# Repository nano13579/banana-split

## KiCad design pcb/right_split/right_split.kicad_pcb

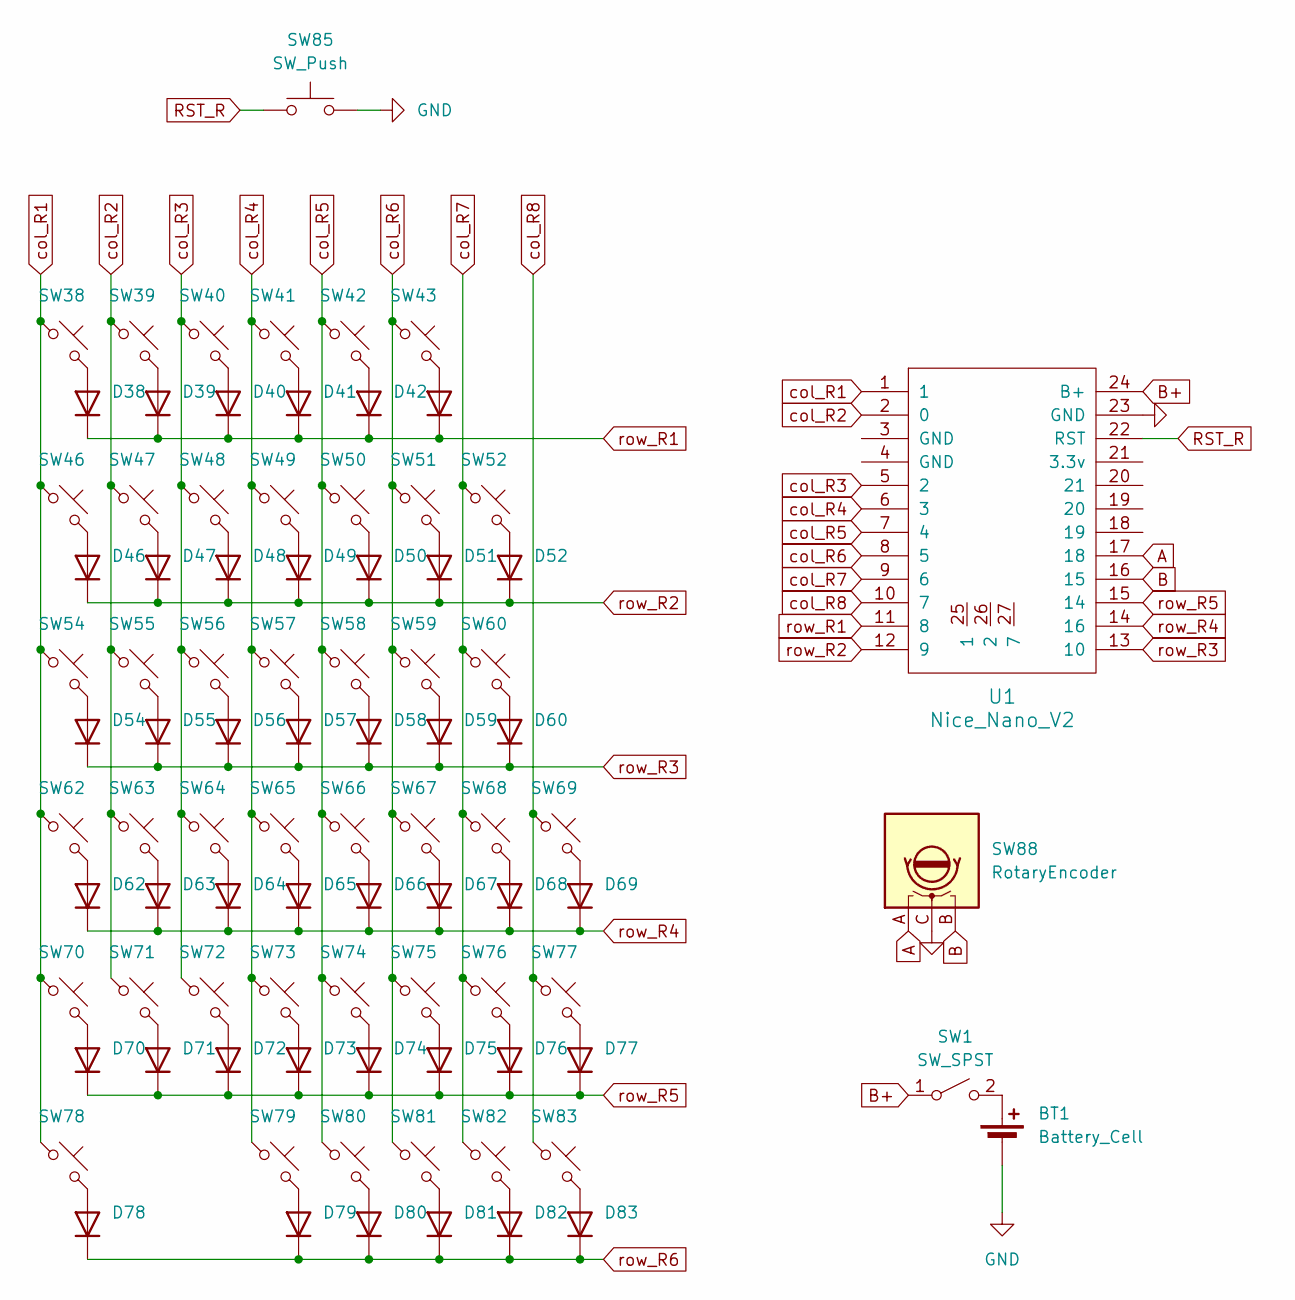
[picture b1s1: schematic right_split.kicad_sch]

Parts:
BT1: Battery_Cell; JST_PH_S2B-PH-K_1x02_P2.00mm_Horizontal
D38, D39, D40, D41, D42, D43, D46, D47, D48, D49, D50, D51, D52, D54, D55, D56, D57, D58, D59, D60, D62, D63, D64, D65, D66, D67, D68, D69, D70, D71, D72, D73, D74, D75, D76, D77, D78, D79, D80, D81, D82, D83: 1N4148; D_DO-35_SOD27_P7.62mm_Horizontal
SW1: SW_SPST; SW_SPST_Omron_B3F-40xx
SW38, SW39, SW40, SW41, SW42, SW43, SW46, SW47, SW48, SW49, SW50, SW51, SW54, SW55, SW56, SW57, SW58, SW59, SW62, SW63, SW64, SW65, SW66, SW67, SW69, SW70, SW71, SW72, SW73, SW74, SW76, SW77, SW83: SW_Push_45deg; MX-Hotswap-1U
SW52: SW_Push_45deg; MX-Hotswap-2U
SW60, SW82: SW_Push_45deg; MX-Hotswap-1.5U
SW68: SW_Push_45deg; MX-Hotswap-2.25U
SW75: SW_Push_45deg; MX-Hotswap-1.75U
SW78: SW_Push_45deg; MX-Hotswap-3U
SW79, SW80, SW81: SW_Push_45deg; MX-Hotswap-1.25U
SW85: SW_Push; SW_PUSH_6mm
SW88: RotaryEncoder; RotaryEncoder_Alps_EC11E-Switch_Vertical_H20mm
U1: Nice_Nano_V2

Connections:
A: SW88.A, U1.17 (18)
B: SW88.B, U1.16 (15)
B+: SW1.1 (A), U1.24 (B+)
GND: BT1.2 (-), SW85.2
GND_MCU2: SW88.C, U1.23 (GND)
unnamed: BT1.1 (+), SW1.2 (B)
unnamed: D38.2 (A), SW38.2
unnamed: D39.2 (A), SW39.2
unnamed: D40.2 (A), SW40.2
unnamed: D41.2 (A), SW41.2
unnamed: D42.2 (A), SW42.2
unnamed: D43.2 (A), SW43.2
unnamed: D46.2 (A), SW46.2
unnamed: D47.2 (A), SW47.2
unnamed: D48.2 (A), SW48.2
unnamed: D49.2 (A), SW49.2
unnamed: D50.2 (A), SW50.2
unnamed: D51.2 (A), SW51.2
unnamed: D52.2 (A), SW52.2
unnamed: D54.2 (A), SW54.2
unnamed: D55.2 (A), SW55.2
unnamed: D56.2 (A), SW56.2
unnamed: D57.2 (A), SW57.2
unnamed: D58.2 (A), SW58.2
unnamed: D59.2 (A), SW59.2
unnamed: D60.2 (A), SW60.2
unnamed: D62.2 (A), SW62.2
unnamed: D63.2 (A), SW63.2
unnamed: D64.2 (A), SW64.2
unnamed: D65.2 (A), SW65.2
unnamed: D66.2 (A), SW66.2
unnamed: D67.2 (A), SW67.2
unnamed: D68.2 (A), SW68.2
unnamed: D69.2 (A), SW69.2
unnamed: D70.2 (A), SW70.2
unnamed: D71.2 (A), SW71.2
unnamed: D72.2 (A), SW72.2
unnamed: D73.2 (A), SW73.2
unnamed: D74.2 (A), SW74.2
unnamed: D75.2 (A), SW75.2
unnamed: D76.2 (A), SW76.2
unnamed: D77.2 (A), SW77.2
unnamed: D78.2 (A), SW78.2
unnamed: D79.2 (A), SW79.2
unnamed: D80.2 (A), SW80.2
unnamed: D81.2 (A), SW81.2
unnamed: D82.2 (A), SW82.2
unnamed: D83.2 (A), SW83.2
RST_R: SW85.1, U1.22 (RST)
col_R1: SW38.1, SW46.1, SW54.1, SW62.1, SW70.1, SW78.1, U1.1
col_R2: SW39.1, SW47.1, SW55.1, SW63.1, SW71.1, U1.2 (0)
col_R3: SW40.1, SW48.1, SW56.1, SW64.1, SW72.1, U1.5 (2)
col_R4: SW41.1, SW49.1, SW57.1, SW65.1, SW73.1, SW79.1, U1.6 (3)
col_R5: SW42.1, SW50.1, SW58.1, SW66.1, SW74.1, SW80.1, U1.7 (4)
col_R6: SW43.1, SW51.1, SW59.1, SW67.1, SW75.1, SW81.1, U1.8 (5)
col_R7: SW52.1, SW60.1, SW68.1, SW76.1, SW82.1, U1.9 (6)
col_R8: SW69.1, SW77.1, SW83.1, U1.10 (7); also elsewhere on the board
row_R1: D38.1 (K), D39.1 (K), D40.1 (K), D41.1 (K), D42.1 (K), D43.1 (K), U1.11 (8)
row_R2: D46.1 (K), D47.1 (K), D48.1 (K), D49.1 (K), D50.1 (K), D51.1 (K), D52.1 (K), U1.12 (9); also elsewhere on the board
row_R3: D54.1 (K), D55.1 (K), D56.1 (K), D57.1 (K), D58.1 (K), D59.1 (K), D60.1 (K), U1.13 (10); also elsewhere on the board
row_R4: D62.1 (K), D63.1 (K), D64.1 (K), D65.1 (K), D66.1 (K), D67.1 (K), D68.1 (K), D69.1 (K), U1.14 (16)
row_R5: D70.1 (K), D71.1 (K), D72.1 (K), D73.1 (K), D74.1 (K), D75.1 (K), D76.1 (K), D77.1 (K), U1.15 (14)
row_R6: D78.1 (K), D79.1 (K), D80.1 (K), D81.1 (K), D82.1 (K), D83.1 (K)

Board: 2 copper layers, 93 parts (0 on the bottom side), 65 nets, no tracks yet.

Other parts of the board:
D53, D61: 1N4148; D_DO-35_SOD27_P7.62mm_Horizontal
SW53, SW61: SW_Push_45deg; MX-Hotswap-1U

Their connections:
unnamed: D53.2 (A), SW53.2
unnamed: D61.2 (A), SW61.2
col_R8: SW53.1, SW61.1; also elsewhere on the board
row_R2: D53.1 (K); also elsewhere on the board
row_R3: D61.1 (K); also elsewhere on the board

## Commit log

2025-07-04 first update
2025-07-05 second update
2025-07-10 third update
